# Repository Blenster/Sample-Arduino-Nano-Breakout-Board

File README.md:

# Sample-Arduino-Nano-Breakout-Board
Sample KiCAD project used as a base for an intro to KiCAD class

This is not a real project and is designed, intentionally, to not do anything in particular. Instead it is just a way I can show folks how to do a couple of simple sample actions in their own projects such as connecting an LED or a switch using through-hole and surface mount parts. There is one "place through via" trace as well.

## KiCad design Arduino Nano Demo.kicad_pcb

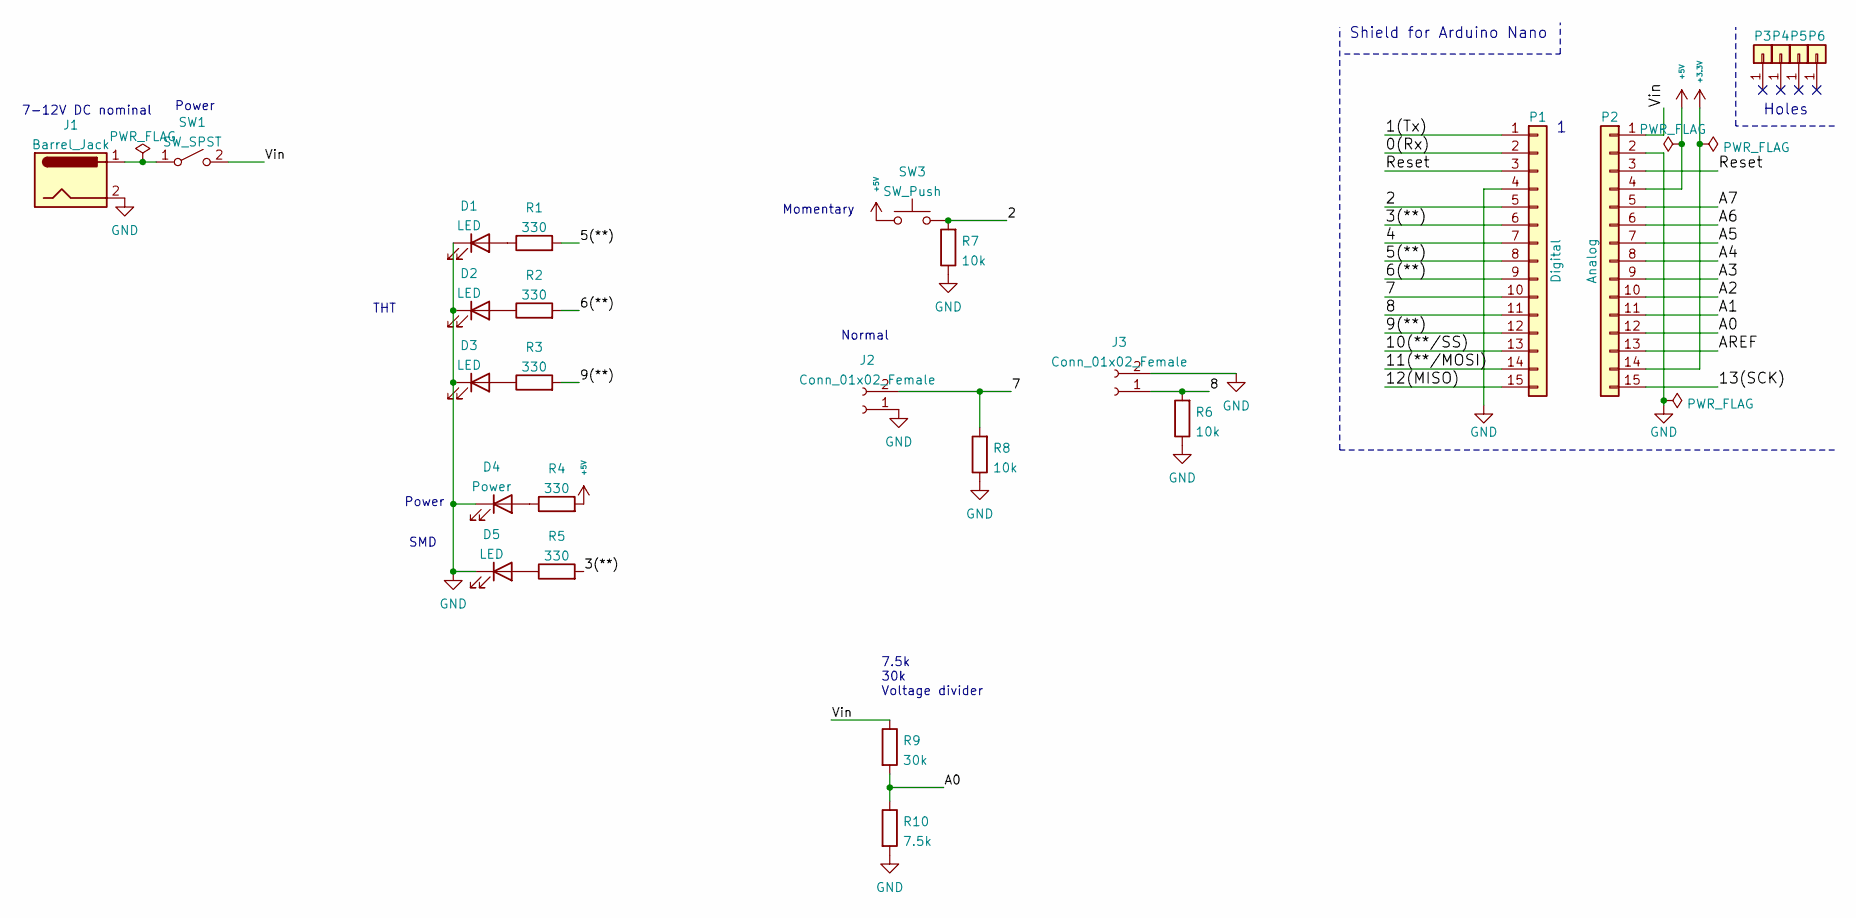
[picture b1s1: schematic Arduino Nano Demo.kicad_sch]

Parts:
D1, D2, D3: LED; LED_D5.0mm
D4: Power; LED_0805_2012Metric
D5: LED; LED_0805_2012Metric
J1: Barrel_Jack; BarrelJack_CUI_PJ-063AH_Horizontal
J2, J3: Conn_01x02_Female; JST_EH_B2B-EH-A_1x02_P2.50mm_Vertical
P1: Digital; Socket_Strip_Arduino_1x15
P2: Analog; Socket_Strip_Arduino_1x15
P3, P4, P5, P6: CONN_01X01; 1pin_Nano
R1, R2, R3: 330; R_Axial_DIN0207_L6.3mm_D2.5mm_P10.16mm_Horizontal
R4, R5: 330; R_0805_2012Metric
R6, R7, R8: 10k; R_0805_2012Metric
R9: 30k; R_0805_2012Metric
R10: 7.5k; R_0805_2012Metric
SW1: SW_SPST; SW_Tactile_SPST_Angled_PTS645Vx58-2LFS
SW3: SW_Push; SW_PUSH_6mm

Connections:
+3V3: P2.14
+5V: P2.4, R4.2, SW3.1
/0(Rx): P1.2
/1(Tx): P1.1
/2: P1.5, R7.2, SW3.2
/3(**): P1.6, R5.2
/4: P1.7
/5(**): P1.8, R1.2
/6(**): P1.9, R2.2
/7: J2.2, P1.10, R8.2
/8: J3.1, P1.11, R6.2
/9(**): P1.12, R3.2
/10(**/SS): P1.13
/11(**/MOSI): P1.14
/12(MISO): P1.15
/13(SCK): P2.15
/A0: P2.12, R9.2, R10.1
/A1: P2.11
/A2: P2.10
/A3: P2.9
/A4: P2.8
/A5: P2.7
/A6: P2.6
/A7: P2.5
/AREF: P2.13
/Reset: P1.3, P2.3
/Vin: P2.1, R9.1, SW1.2 (B)
GND: D1.1 (K), D2.1 (K), D3.1 (K), D4.1 (K), D5.1 (K), J1.2, J2.1, J3.2, P1.4, P2.2, R6.1, R7.1, R8.1, R10.2
unnamed: D1.2 (A), R1.1
unnamed: D2.2 (A), R2.1
unnamed: D3.2 (A), R3.1
unnamed: D4.2 (A), R4.1
unnamed: D5.2 (A), R5.1
unnamed: J1.1, SW1.1 (A)

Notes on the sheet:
Holes
Shield for Arduino Nano
SMD
Normal
7.5k 30k Voltage divider
7-12V DC nominal
Power
THT
Momentary

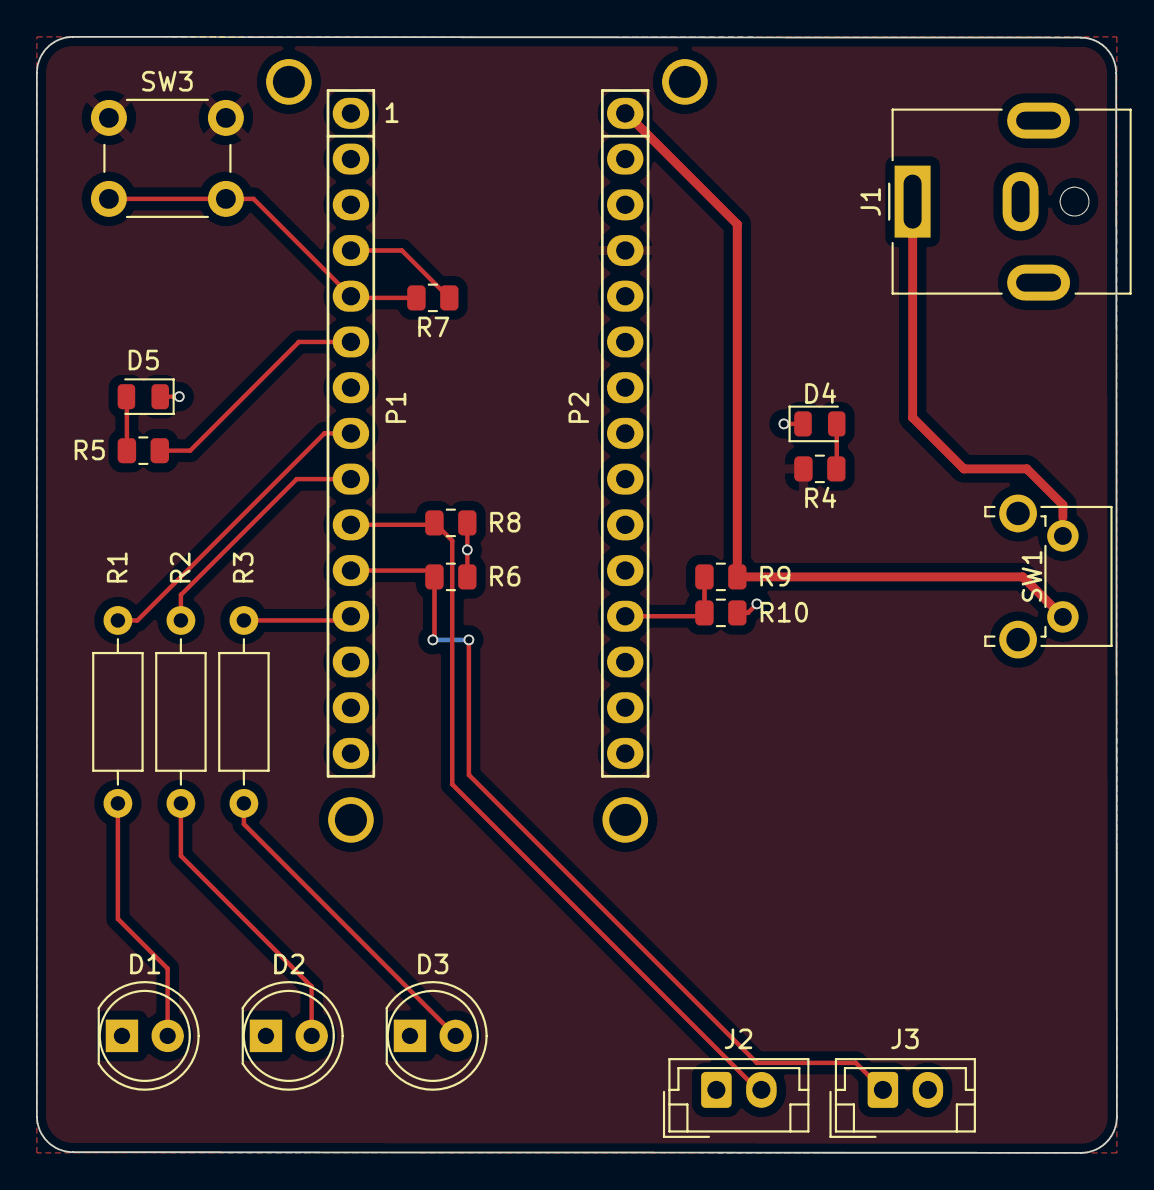
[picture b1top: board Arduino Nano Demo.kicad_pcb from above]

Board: 2 copper layers, 60.0 x 62.0 mm, 26 parts (0 on the bottom side), 18 nets.

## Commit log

2022-02-10 Initial Commit
    Initial commit; after replacing the switch with pins
2022-02-10 Initial Commit
    No dual-position switch
2022-02-10 Initial edit
    Note: should add more details and class notes here.
2022-02-11 Added JST connectors
    Found some nice JST plugs to add for the inputs; makes more sense to have grounds for them anyway. Cool 3D models and everything.
2022-02-24 Minor Tweaks
    Based on feedback I tweaked the example schematic a little bit; all formatting/positioning stuff --- no real changes
